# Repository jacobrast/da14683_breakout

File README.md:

View this project on [CADLAB.io](https://cadlab.io/project/2404). 

# da14683_breakout

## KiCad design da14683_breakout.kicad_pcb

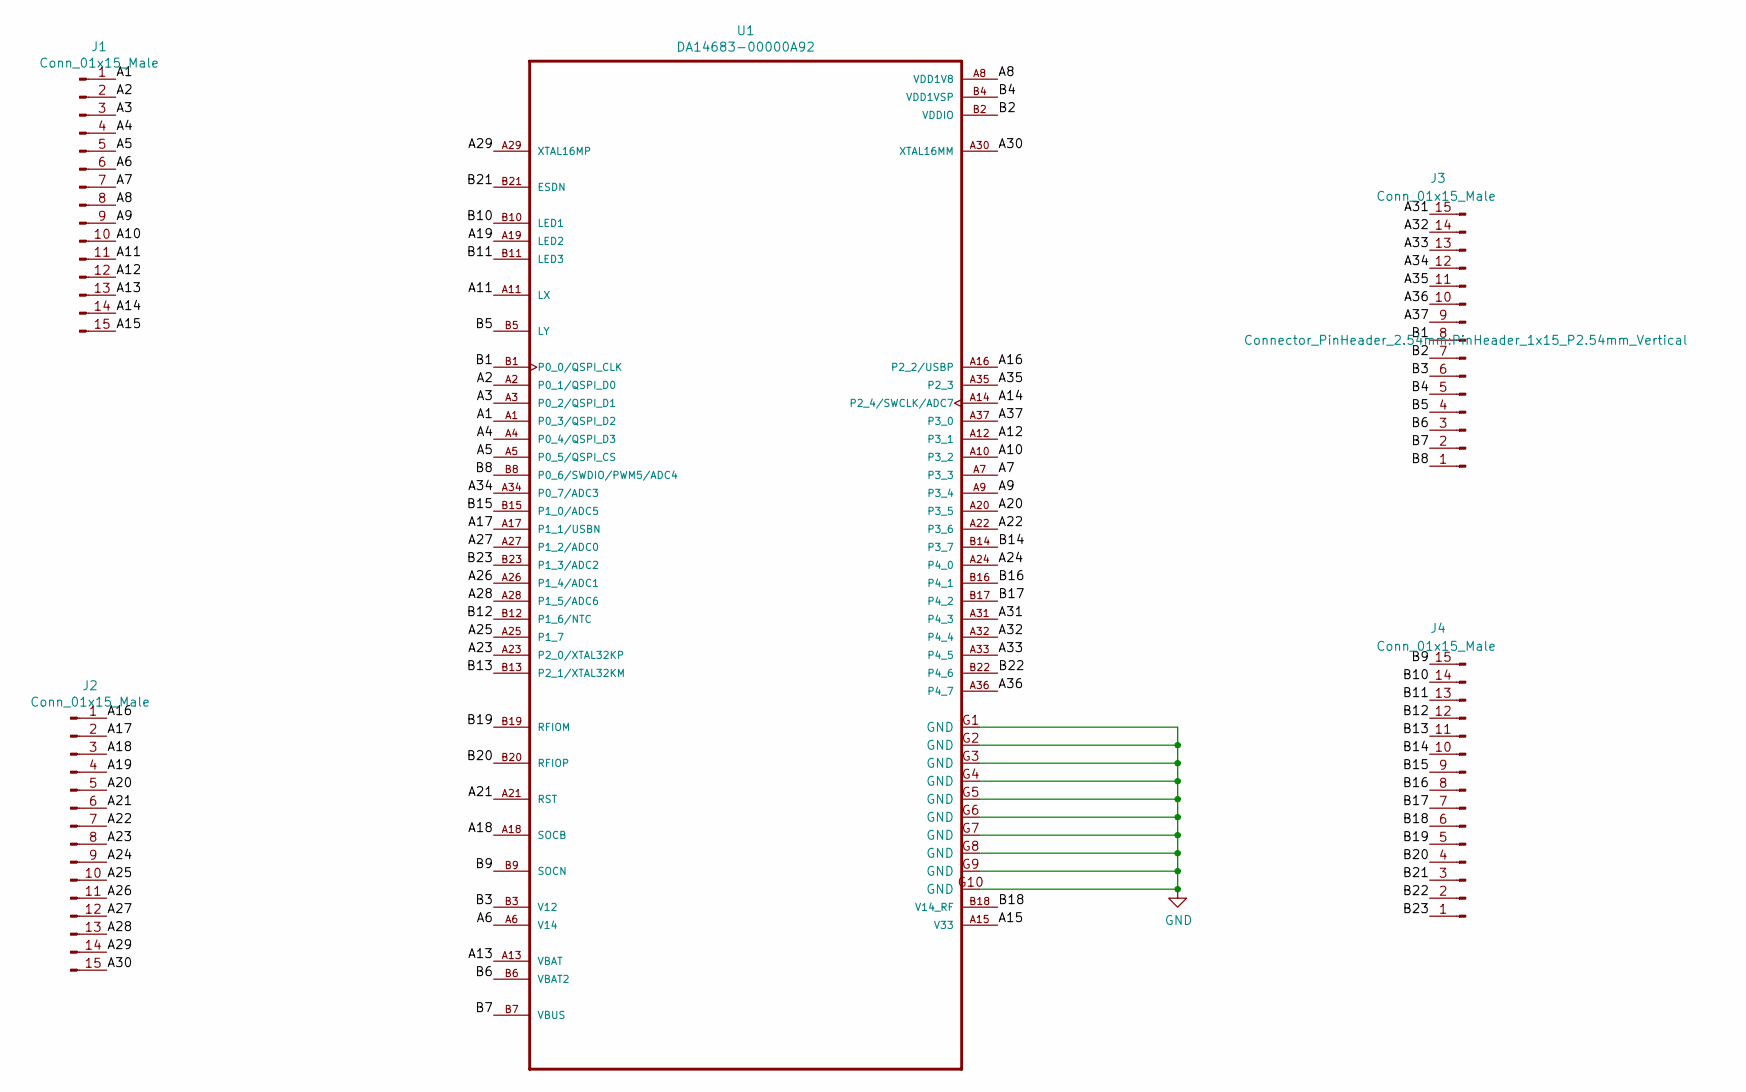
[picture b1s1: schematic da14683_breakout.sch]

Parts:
J1, J2, J3, J4: Conn_01x15_Male; PinHeader_1x15_P2.54mm_Vertical
U1: DA14683-00000A92; XCVR_DA14680-01F08A92

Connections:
/A1: J1.1, U1.A1 (P0_3/QSPI_D2)
/A2: J1.2, U1.A2 (P0_1/QSPI_D0)
/A3: J1.3, U1.A3 (P0_2/QSPI_D1)
/A4: J1.4, U1.A4 (P0_4/QSPI_D3)
/A5: J1.5, U1.A5 (P0_5/QSPI_CS)
/A6: J1.6, U1.A6 (V14)
/A7: J1.7, U1.A7 (P3_3)
/A8: J1.8, U1.A8 (VDD1V8)
/A9: J1.9, U1.A9 (P3_4)
/A10: J1.10, U1.A10 (P3_2)
/A11: J1.11, U1.A11 (LX)
/A12: J1.12, U1.A12 (P3_1)
/A13: J1.13, U1.A13 (VBAT)
/A14: J1.14, U1.A14 (P2_4/SWCLK/ADC7)
/A15: J1.15, U1.A15 (V33)
/A16: J2.1, U1.A16 (P2_2/USBP)
/A17: J2.2, U1.A17 (P1_1/USBN)
/A18: J2.3, U1.A18 (SOCB)
/A19: J2.4, U1.A19 (LED2)
/A20: J2.5, U1.A20 (P3_5)
/A21: J2.6, U1.A21 (RST)
/A22: J2.7, U1.A22 (P3_6)
/A23: J2.8, U1.A23 (P2_0/XTAL32KP)
/A24: J2.9, U1.A24 (P4_0)
/A25: J2.10, U1.A25 (P1_7)
/A26: J2.11, U1.A26 (P1_4/ADC1)
/A27: J2.12, U1.A27 (P1_2/ADC0)
/A28: J2.13, U1.A28 (P1_5/ADC6)
/A29: J2.14, U1.A29 (XTAL16MP)
/A30: J2.15, U1.A30 (XTAL16MM)
/A31: J3.15, U1.A31 (P4_3)
/A32: J3.14, U1.A32 (P4_4)
/A33: J3.13, U1.A33 (P4_5)
/A34: J3.12, U1.A34 (P0_7/ADC3)
/A35: J3.11, U1.A35 (P2_3)
/A36: J3.10, U1.A36 (P4_7)
/A37: J3.9, U1.A37 (P3_0)
/B1: J3.8, U1.B1 (P0_0/QSPI_CLK)
/B2: J3.7, U1.B2 (VDDIO)
/B3: J3.6, U1.B3 (V12)
/B4: J3.5, U1.B4 (VDD1VSP)
/B5: J3.4, U1.B5 (LY)
/B6: J3.3, U1.B6 (VBAT2)
/B7: J3.2, U1.B7 (VBUS)
/B8: J3.1, U1.B8 (P0_6/SWDIO/PWM5/ADC4)
/B9: J4.15, U1.B9 (SOCN)
/B10: J4.14, U1.B10 (LED1)
/B11: J4.13, U1.B11 (LED3)
/B12: J4.12, U1.B12 (P1_6/NTC)
/B13: J4.11, U1.B13 (P2_1/XTAL32KM)
/B14: J4.10, U1.B14 (P3_7)
/B15: J4.9, U1.B15 (P1_0/ADC5)
/B16: J4.8, U1.B16 (P4_1)
/B17: J4.7, U1.B17 (P4_2)
/B18: J4.6, U1.B18 (V14_RF)
/B19: J4.5, U1.B19 (RFIOM)
/B20: J4.4, U1.B20 (RFIOP)
/B21: J4.3, U1.B21 (ESDN)
/B22: J4.2, U1.B22 (P4_6)
/B23: J4.1, U1.B23 (P1_3/ADC2)

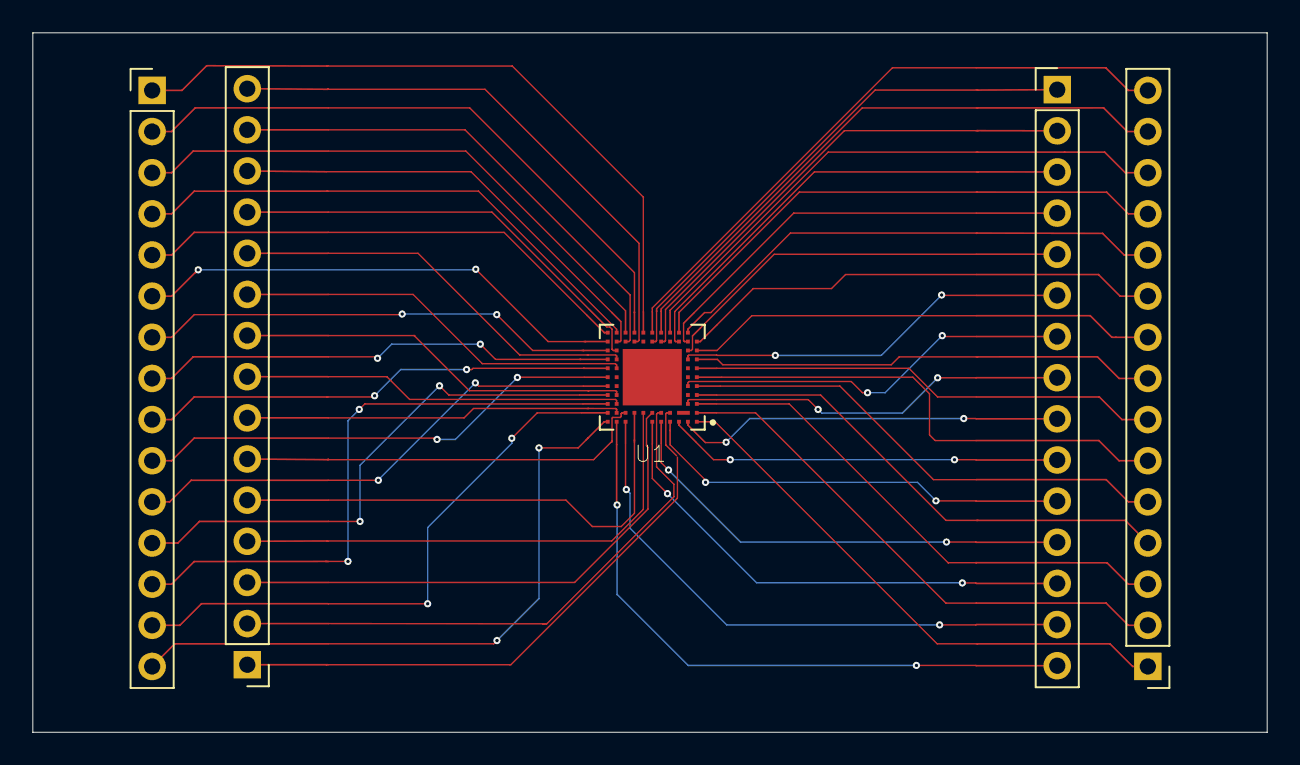
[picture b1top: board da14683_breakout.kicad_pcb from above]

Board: 2 copper layers, 76.2 x 43.2 mm, 5 parts (0 on the bottom side), 60 nets.

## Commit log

2020-01-09 Backlink to CADLAB.io has been added.
2020-01-14 Wired PCB
